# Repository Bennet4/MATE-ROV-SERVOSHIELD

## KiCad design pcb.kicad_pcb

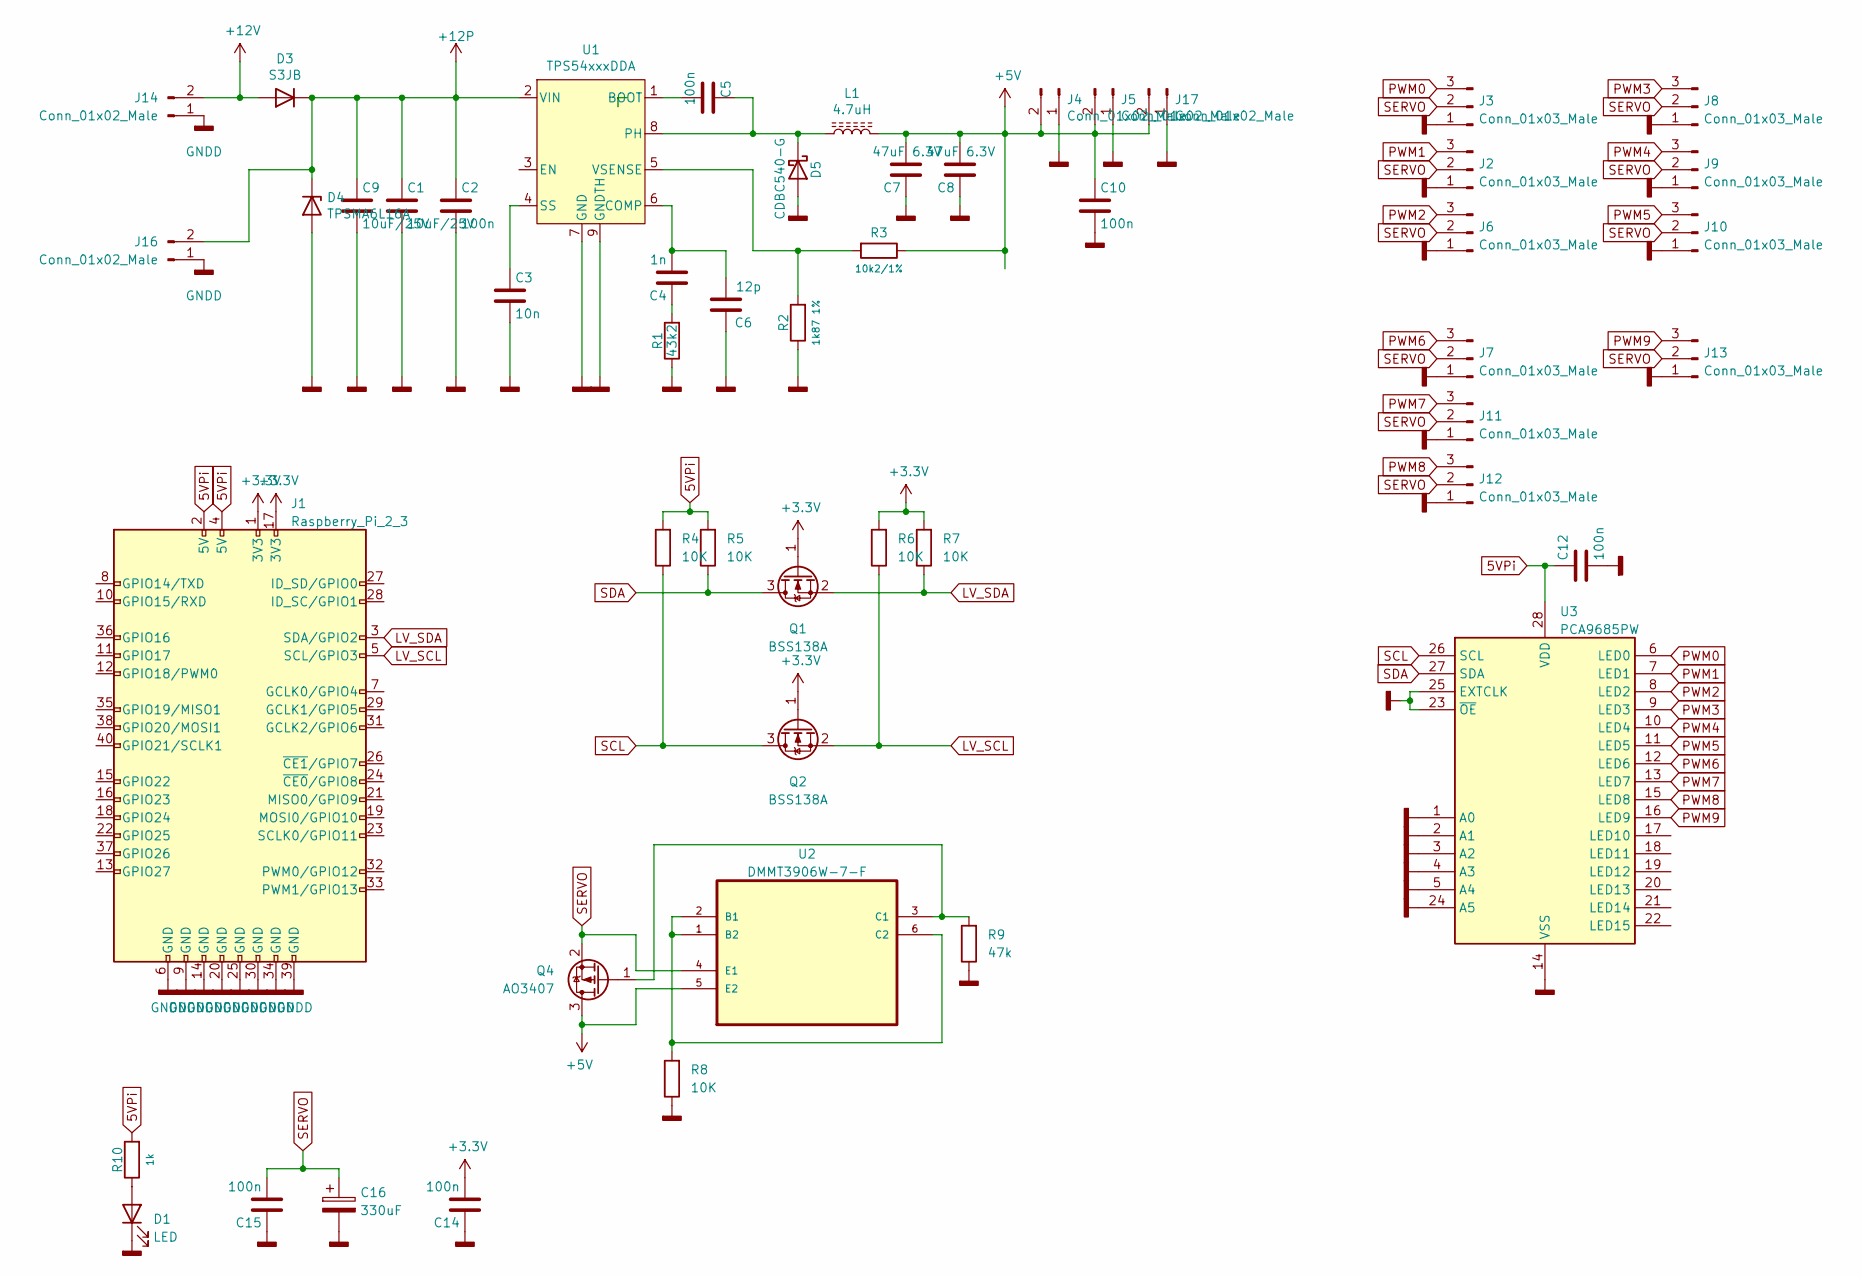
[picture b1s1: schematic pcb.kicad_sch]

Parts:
C1, C9: 10uF/25V; C_0805_2012Metric
C2, C5, C10, C12, C14, C15: 100n; C_0603_1608Metric
C3: 10n; C_0603_1608Metric
C4: 1n; C_0603_1608Metric
C6: 12p; C_0603_1608Metric
C7, C8: 47uF 6.3V; C_1210_3225Metric
C16: 330uF; CP_Radial_D10.0mm_P5.00mm
D1: LED; LED_0603_1608Metric
D3: S3JB; D_SMB
D4: TPSMA6L16A; D_SMA
D5: CDBC540-G; D_SMC
J1: Raspberry_Pi_2_3; PinSocket_2x20_P2.54mm_Vertical
J2, J3, J6, J7, J8, J9, J10, J11, J12, J13: Conn_01x03_Male; JST_XH_B3B-XH-A_1x03_P2.50mm_Vertical
J4, J5, J14, J16, J17: Conn_01x02_Male; JST_XH_B2B-XH-A_1x02_P2.50mm_Vertical
L1: 4.7uH; DR127
Q1, Q2: BSS138A; SOT-23
Q4: AO3407; SOT-23
R1: 43k2; R_0603_1608Metric
R2: 1k87 1%; R_0603_1608Metric
R3: 10k2/1%; R_0603_1608Metric
R4, R5, R6, R7, R8: 10K; R_0603_1608Metric
R9: 47k; R_0603_1608Metric
R10: 1k; R_0603_1608Metric
U1: TPS54xxxDDA; HSOP-8-1EP_3.9x4.9mm_P1.27mm_EP2.41x3.1mm_ThermalVias
U2: DMMT3906W-7-F; SOT-363_SC-70-6; MPN DMMT3906W-7-F
U3: PCA9685PW; TSSOP-28_4.4x9.7mm_P0.65mm

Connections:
5VPi: C12.1, J1.2 (5V), J1.4 (5V), R4.2, R5.2, R10.2, U3.28 (VDD)
+3.3V: C14.2, J1.1 (3V3), J1.17 (3V3), Q1.1 (G), Q2.1 (G), R6.2, R7.2
+5V: C7.2, C8.2, C10.1, J4.2, J5.2, J17.2, L1.2, Q4.3 (D), R3.1, U2.5 (E2)
+12P: C1.1, C2.1, C9.1, D3.1 (K), D4.1 (K), J16.2, U1.2 (VIN)
+12V: D3.2 (A), J14.2
GNDD: C1.2, C2.2, C3.2, C6.1, C7.1, C8.1, C9.2, C10.2, C12.2, C14.1, C15.1, C16.2, D1.1 (K), D4.2 (A), D5.2 (A), J1.6 (GND), J1.9 (GND), J1.14 (GND), J1.20 (GND), J1.25 (GND), J1.30 (GND), J1.34 (GND), J1.39 (GND), J2.1, J3.1, J4.1, J5.1, J6.1, J7.1, J8.1, J9.1, J10.1, J11.1, J12.1, J13.1, J14.1, J16.1, J17.1, R1.1, R2.1, R8.1, R9.1, U1.7 (GND), U1.9 (GNDTH), U3.1 (A0), U3.2 (A1), U3.3 (A2), U3.4 (A3), U3.5 (A4), U3.14 (VSS), U3.23 (~OE), U3.24 (A5), U3.25 (EXTCLK)
LV_SCL: J1.5 (SCL/GPIO3), Q2.2 (S), R6.1
LV_SDA: J1.3 (SDA/GPIO2), Q1.2 (S), R7.1
unnamed: C3.1, U1.4 (SS)
unnamed: C4.1, R1.2
unnamed: C4.2, C6.2, U1.6 (COMP)
unnamed: C5.1, D5.1 (K), L1.1, U1.8 (PH)
unnamed: C5.2, U1.1 (BOOT)
unnamed: D1.2 (A), R10.1
unnamed: Q4.1 (G), R9.2, U2.3 (C1)
unnamed: R2.2, R3.2, U1.5 (VSENSE)
unnamed: R8.2, U2.1 (B2), U2.2 (B1), U2.6 (C2)
PWM0: J3.3, U3.6 (LED0)
PWM1: J2.3, U3.7 (LED1)
PWM2: J6.3, U3.8 (LED2)
PWM3: J8.3, U3.9 (LED3)
PWM4: J9.3, U3.10 (LED4)
PWM5: J10.3, U3.11 (LED5)
PWM6: J7.3, U3.12 (LED6)
PWM7: J11.3, U3.13 (LED7)
PWM8: J12.3, U3.15 (LED8)
PWM9: J13.3, U3.16 (LED9)
SCL: Q2.3 (D), R4.1, U3.26 (SCL)
SDA: Q1.3 (D), R5.1, U3.27 (SDA)
SERVO: C15.2, C16.1, J2.2, J3.2, J6.2, J7.2, J8.2, J9.2, J10.2, J11.2, J12.2, J13.2, Q4.2 (S), U2.4 (E1)

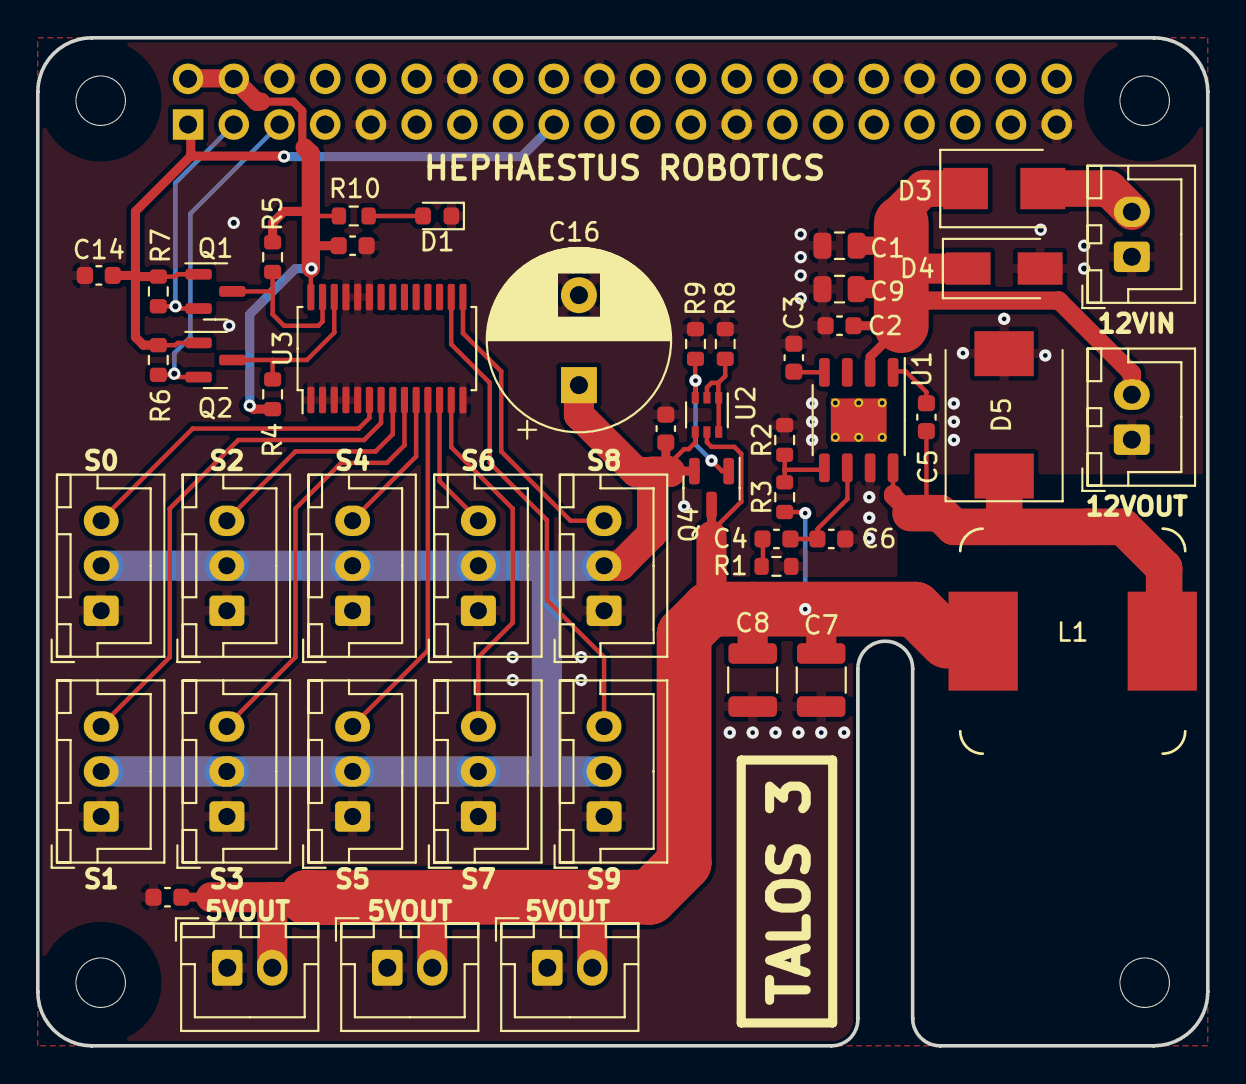
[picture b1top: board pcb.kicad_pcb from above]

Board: 2 copper layers, 65.0 x 56.0 mm, 51 parts (1 on the bottom side), 30 nets.

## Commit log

2023-02-14 Files added
2023-02-14 added images & plug placement
2023-02-14 added reverse current protection
2023-02-26 FInalized layout
    DRC checked
2023-02-26 uploaded finalized pictures
2023-02-26 added logos
2023-02-27 Added slit for ribbon cable from pi camera
2023-03-04 final version sent to fabrication
